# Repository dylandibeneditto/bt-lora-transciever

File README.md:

# bt-lora-transciever

## SX1262 (LoRa)
(datasheet)
https://semtech.my.salesforce.com/sfc/p/#E0000000JelG/a/RQ000008nKCH/hp2iKwMDKWl34g1D3LBf_zC7TGBRIo2ff5LMnS8r19s
(application notes)
https://cdn-reichelt.de/documents/datenblatt/A200/SX1262REFERENCE.pdf

## Matching Network IC (0900FM15K0039001E)
https://www.johansontechnology.com/docs/1646/0900FM15K0039001E_rIWs6SY.pdf
https://www.johansontechnology.com/docs/2424/oldjti-an100_kC6DtU1.pdf

## nRF21540 (Bluetooth Range Extender)
https://docs.nordicsemi.com/r/bundle/ps_nrf21540/page/chapters/hw_layout/reference_circuitry/doc/alt1.html

## nRF52840
https://docs.nordicsemi.com/r/bundle/ps_nrf52840/page/keyfeatures_html5.html

## 3.3V LDO (LD39200)
https://www.st.com/content/ccc/resource/technical/document/datasheet/4b/e6/2e/a4/16/04/46/9d/DM00102135.pdf/files/DM00102135.pdf/jcr:content/translations/en.DM00102135.pdf

## 5V Buck (TPS51386)
https://www.ti.com/lit/ds/symlink/tps51386.pdf?ts=1792470785772&ref_url=https%253A%252F%252Fwww.ti.com%252Fproduct%252FTPS51386%252Fpart-details%252FTPS51386RJNR%253Futm_source%253Dgoogle%2526utm_medium%253Dcpc%2526utm_campaign%253Dapp-null-null-app_opn_en-cpc-storeic-google-ww_en_pur%2526utm_content%253DDevice%2526ds_k%253DTPS51386RJNR%2526DCM%253Dyes%2526gclsrc%253Daw.ds%2526gad_source%253D1%2526gad_campaignid%253D18950597671%2526gbraid%253D0AAAAAC068F2AgVPJnnzCa5HBOf_R-twsL%2526gclid%253DCjwKCAjw_9bWBhBGEiwAomyTIuwXhYG7RjTolWD5RO6H10wT5wzYAQIXjeRW8OVubMzsjR8nUko-0RoCKO8QAvD_BwE

## TCXO (ECS-TXO-20SCMV4)
https://ecsxtal.com/store/pdf/ECS-TXO-20CSMV4.pdf

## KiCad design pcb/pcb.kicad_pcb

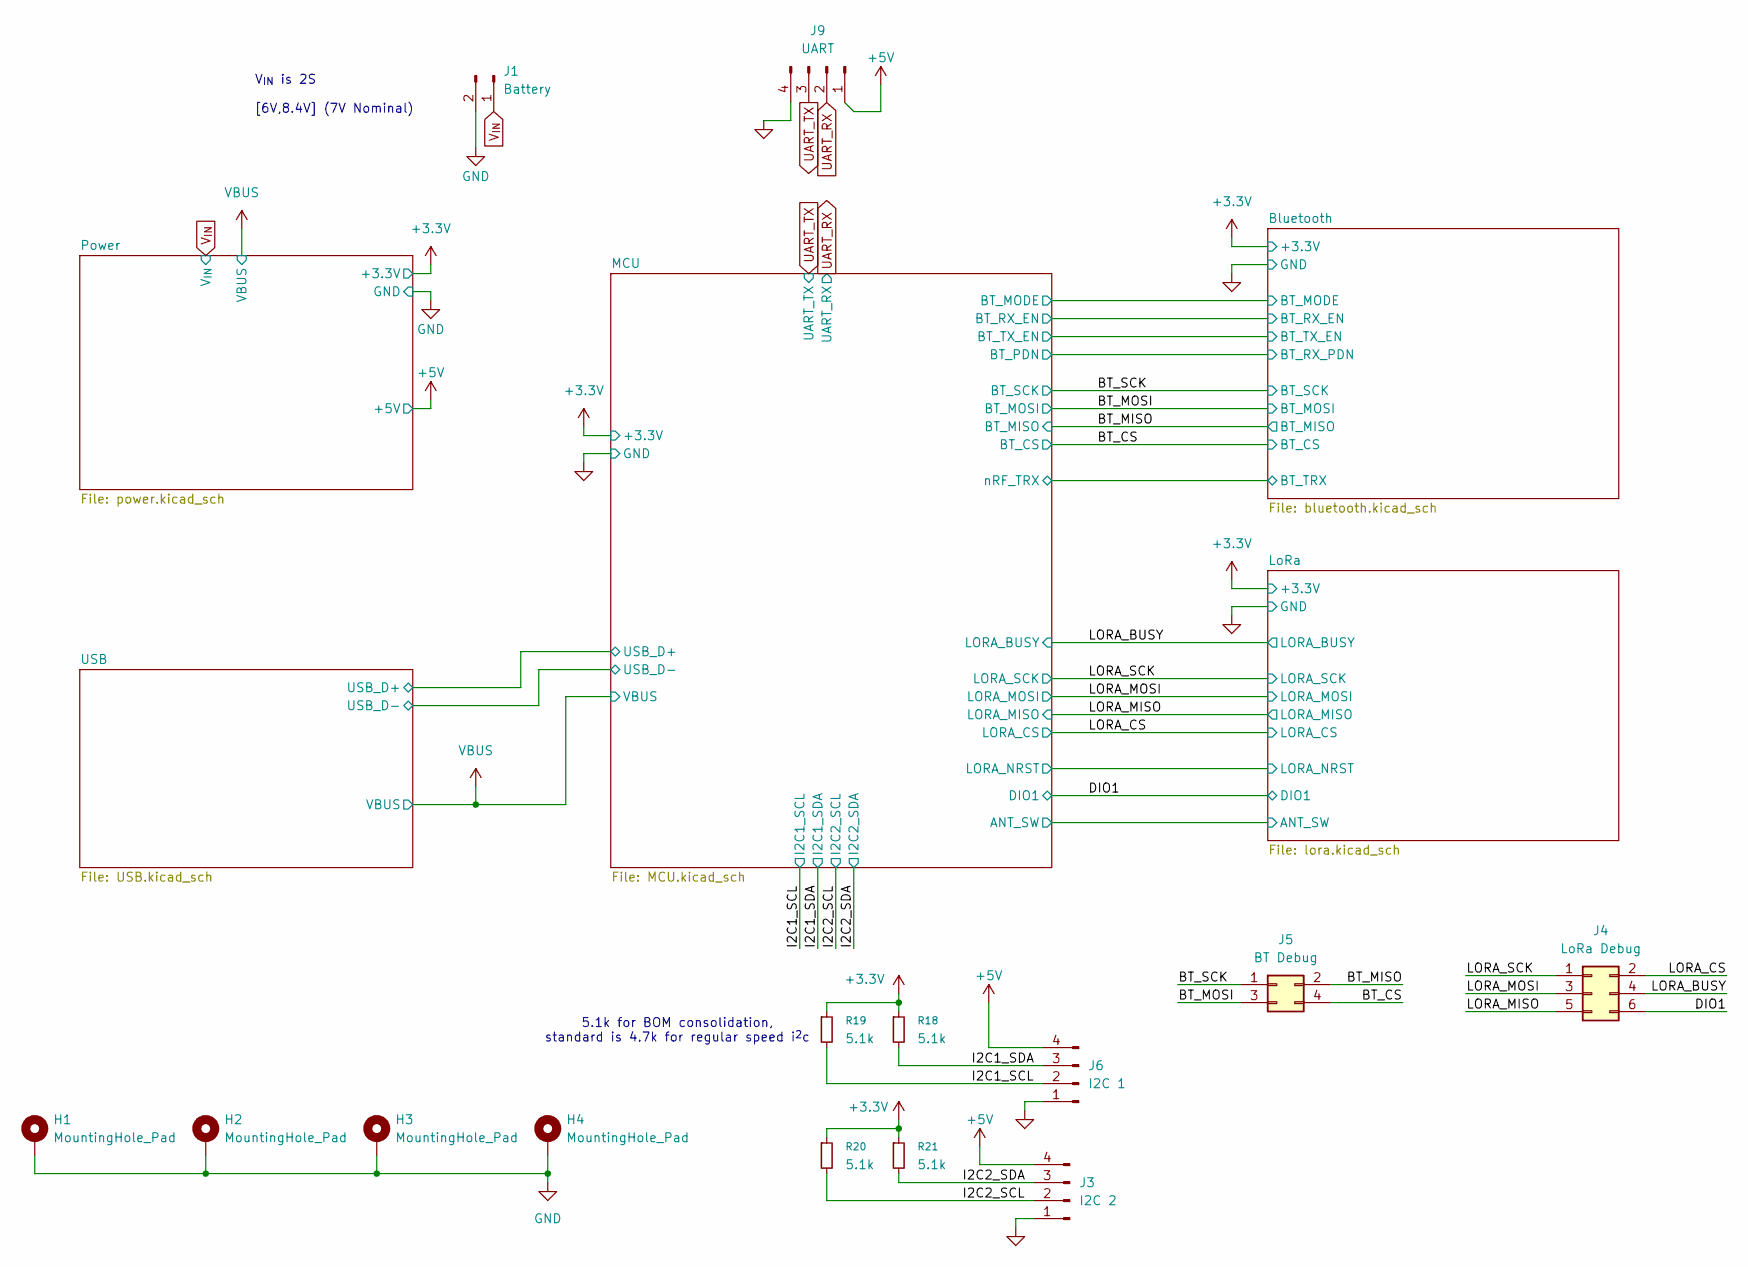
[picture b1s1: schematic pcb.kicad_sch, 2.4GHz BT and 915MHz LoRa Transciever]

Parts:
H1, H2, H3, H4: MountingHole_Pad; MountingHole_2.2mm_M2_Pad_Via
J1: Battery; JST_GH_SM02B-GHS-TB_1x02-1MP_P1.25mm_Horizontal
J3: I2C 2; JST_GH_SM04B-GHS-TB_1x04-1MP_P1.25mm_Horizontal
J4: LoRa Debug; PinHeader_2x03_P2.54mm_Vertical
J5: BT Debug; PinHeader_2x02_P2.54mm_Vertical
J6: I2C 1; JST_GH_SM04B-GHS-TB_1x04-1MP_P1.25mm_Horizontal
J9: UART; JST_GH_SM04B-GHS-TB_1x04-1MP_P1.25mm_Horizontal
R18, R19, R20, R21: 5.1k; R_0603_1608Metric

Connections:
+3.3V: R18.1, R19.1, R20.1, R21.1; also elsewhere on the board
+5V: J3.4, J6.4, J9.1; also elsewhere on the board
BT_CS: J5.4; also elsewhere on the board
BT_MISO: J5.2; also elsewhere on the board
BT_MOSI: J5.3; also elsewhere on the board
BT_SCK: J5.1; also elsewhere on the board
DIO1: J4.6; also elsewhere on the board
GND: H1.1 (1_1), H2.1 (1_1), H3.1 (1_1), H4.1 (1_1), J1.2, J3.1, J6.1, J9.4; also elsewhere on the board
I2C1_SCL: J6.2, R19.2; also elsewhere on the board
I2C1_SDA: J6.3, R18.2; also elsewhere on the board
I2C2_SCL: J3.2, R20.2; also elsewhere on the board
I2C2_SDA: J3.3, R21.2; also elsewhere on the board
LORA_BUSY: J4.4; also elsewhere on the board
LORA_CS: J4.2; also elsewhere on the board
LORA_MISO: J4.5; also elsewhere on the board
LORA_MOSI: J4.3; also elsewhere on the board
LORA_SCK: J4.1; also elsewhere on the board
UART_RX: J9.2; also elsewhere on the board
UART_TX: J9.3; also elsewhere on the board
V_{IN}: J1.1; also elsewhere on the board

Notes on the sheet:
V_{IN} is 2S [6V,8.4V] (7V Nominal)
5.1k for BOM consolidation, standard is 4.7k for regular speed i^{2}c

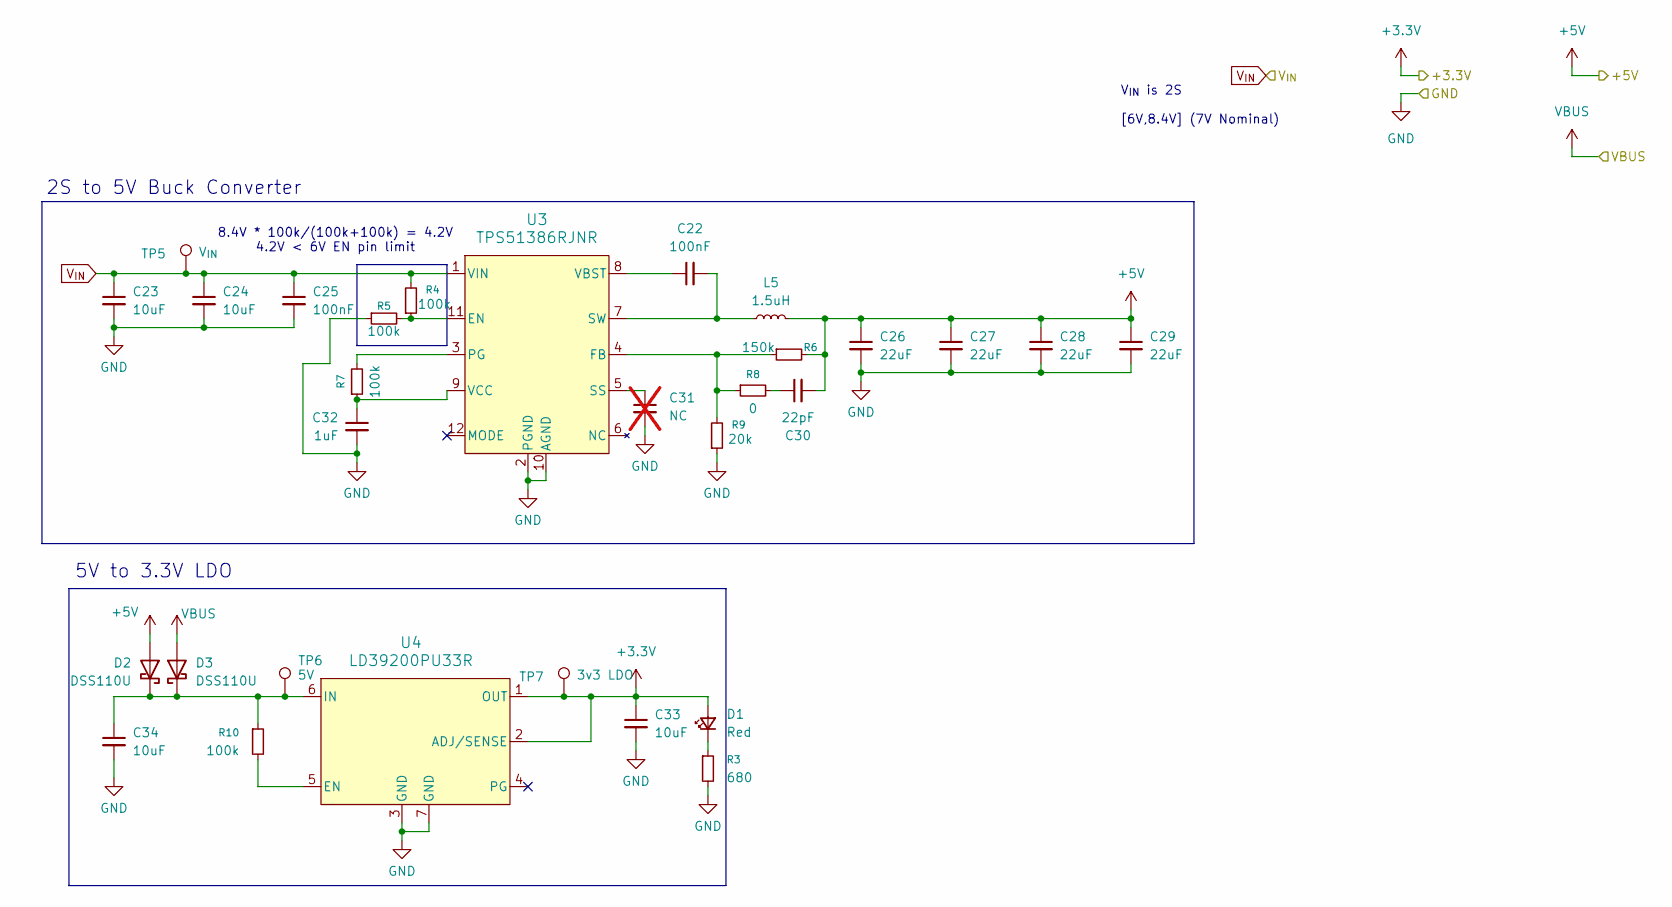
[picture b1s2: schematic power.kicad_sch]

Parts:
C22, C25: 100nF; C_0402_1005Metric
C23, C24, C33, C34: 10uF; C_0805_2012Metric
C26, C27, C28, C29: 22uF; C_0805_2012Metric
C30: 22pF; C_0402_1005Metric
C31: NC; C_0805_2012Metric; not fitted
C32: 1uF; C_0805_2012Metric
D1: Red; LED_0603_1608Metric
D2, D3: DSS110U; D_SOD-123F
L5: 1.5uH; L_Coilcraft_XAL6030-XXX
R3: 680; R_0603_1608Metric
R4, R5, R7, R10: 100k; R_0603_1608Metric
R6: 150k; R_0603_1608Metric
R8: 0; R_0603_1608Metric
R9: 20k; R_0603_1608Metric
TP5: V_{IN}; TestPoint_Pad_D1.0mm
TP6: 5V; TestPoint_Pad_D1.0mm
TP7: 3v3 LDO; TestPoint_Pad_D1.0mm
U3: TPS51386RJNR; VQFN-HR12_RJN_TEX
U4: LD39200PU33R; SON_DFN6_3X3_STM

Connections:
+3.3V: C33.1, D1.2 (A), TP7.1 (1_1), U4.1 (OUT), U4.2 (ADJ/SENSE); also elsewhere on the board
+5V: C26.1, C27.1, C28.1, C29.1, C30.2, D2.2 (A), L5.2, R6.2; also elsewhere on the board
GND: C23.2, C24.2, C25.2, C26.2, C27.2, C28.2, C29.2, C31.2, C32.2, C33.2, C34.2, R3.2, R5.1, R9.1, U3.2 (PGND), U3.10 (AGND), U4.3 (GND), U4.7 (GND); also elsewhere on the board
unnamed: C30.1, R8.2
unnamed: D1.1 (K), R3.1
unnamed: C34.1, D2.1 (K), D3.1 (K), R10.1, TP6.1 (1_1), U4.6 (IN)
unnamed: R4.1, R5.2, U3.11 (EN)
unnamed: R6.1, R8.1, R9.2, U3.4 (FB)
unnamed: R7.2, U3.3 (PG)
unnamed: C31.1, U3.5 (SS)
unnamed: C22.2, L5.1, U3.7 (SW)
unnamed: C22.1, U3.8 (VBST)
unnamed: C32.1, R7.1, U3.9 (VCC)
unnamed: R10.2, U4.5 (EN)
VBUS: D3.2 (A); also elsewhere on the board
V_{IN}: C23.1, C24.1, C25.1, R4.2, TP5.1 (1_1), U3.1 (VIN); also elsewhere on the board

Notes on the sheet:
2S to 5V Buck Converter
V_{IN} is 2S [6V,8.4V] (7V Nominal)
5V to 3.3V LDO
8.4V * 100k/(100k+100k) = 4.2V 4.2V < 6V EN pin limit

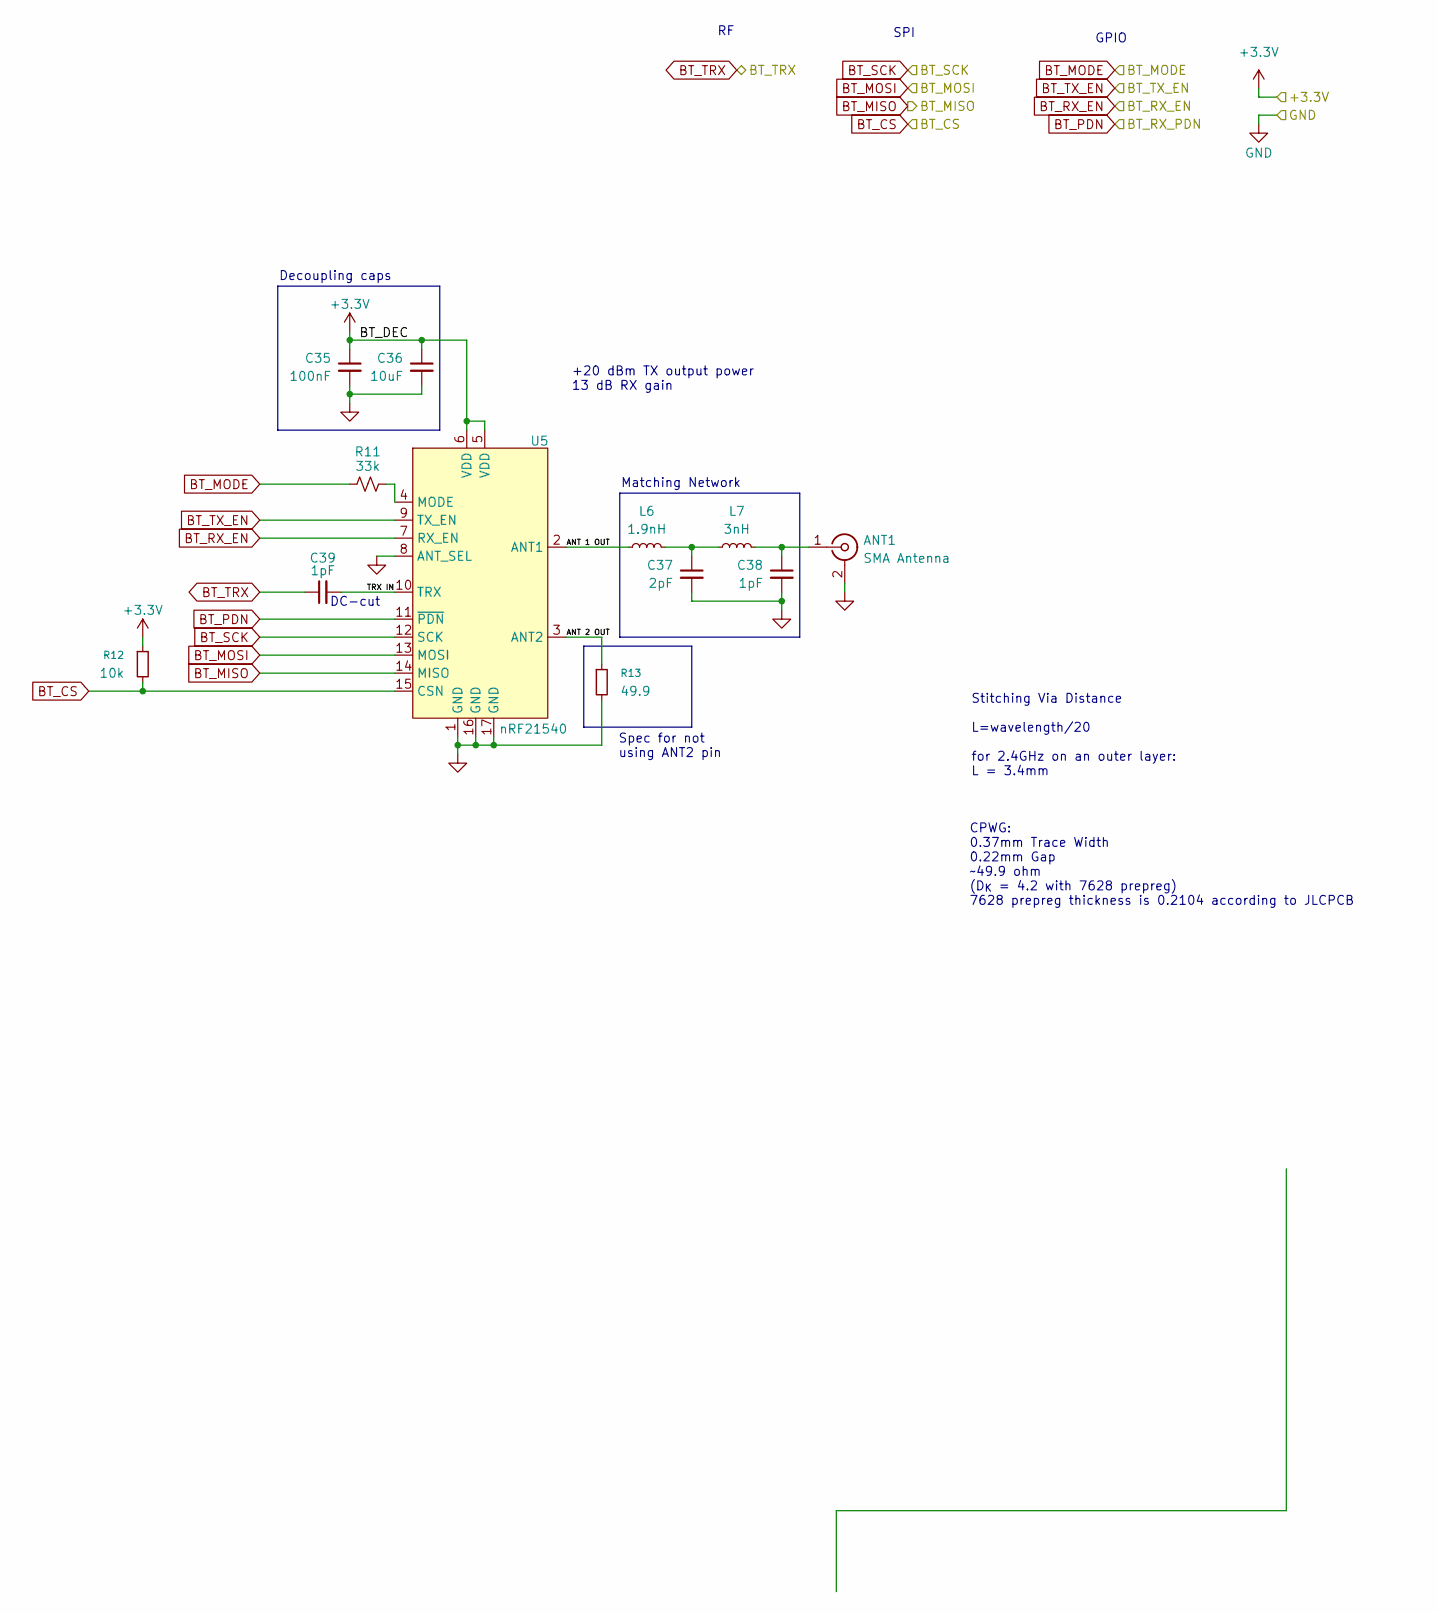
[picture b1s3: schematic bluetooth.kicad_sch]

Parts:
ANT1: SMA Antenna; SMA_Molex_73251-2120_EdgeMount_Horizontal
C35: 100nF; C_0402_1005Metric
C36: 10uF; C_0603_1608Metric
C37: 2pF; C_0402_1005Metric
C38, C39: 1pF; C_0402_1005Metric
L6: 1.9nH; L_0402_1005Metric
L7: 3nH; L_0402_1005Metric
R11: 33k; R_0603_1608Metric
R12: 10k; R_0603_1608Metric
R13: 49.9; R_0603_1608Metric
U5: nRF21540; QFN-16-1EP_4x4mm_P0.65mm_EP2.7x2.7mm

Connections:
+3.3V: C35.1, C36.1, R12.1, U5.5 (VDD), U5.6 (VDD); also elsewhere on the board
/Bluetooth/ANT 1 OUT: L6.1, U5.2 (ANT1)
/Bluetooth/ANT 2 OUT: R13.1, U5.3 (ANT2)
/Bluetooth/TRX IN: C39.2, U5.10 (TRX)
BT_CS: R12.2, U5.15 (CSN); also elsewhere on the board
BT_MISO: U5.14 (MISO); also elsewhere on the board
BT_MODE: R11.1; also elsewhere on the board
BT_MOSI: U5.13 (MOSI); also elsewhere on the board
BT_PDN: U5.11 (~PDN); also elsewhere on the board
BT_RX_EN: U5.7 (RX_EN); also elsewhere on the board
BT_SCK: U5.12 (SCK); also elsewhere on the board
BT_TX_EN: U5.9 (TX_EN); also elsewhere on the board
GND: ANT1.2 (Ext), C35.2, C36.2, C37.2, C38.2, R13.2, U5.1 (GND), U5.8 (ANT_SEL), U5.16 (GND), U5.17 (GND); also elsewhere on the board
unnamed: ANT1.1 (In), C38.1, L7.2
unnamed: C37.1, L6.2, L7.1
unnamed: R11.2, U5.4 (MODE)
nRF_TRX: C39.1; also elsewhere on the board

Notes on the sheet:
CPWG: 0.37mm Trace Width 0.22mm Gap ~49.9 ohm (D_{K} = 4.2 with 7628 prepreg) 7628 prepreg thickness is 0.2104 according to JLCPCB
SPI
DC-cut
+20 dBm TX output power 13 dB RX gain
Spec for not using ANT2 pin
Matching Network
Stitching Via Distance L=wavelength/20 for 2.4GHz on an outer layer: L = 3.4mm
GPIO
Decoupling caps

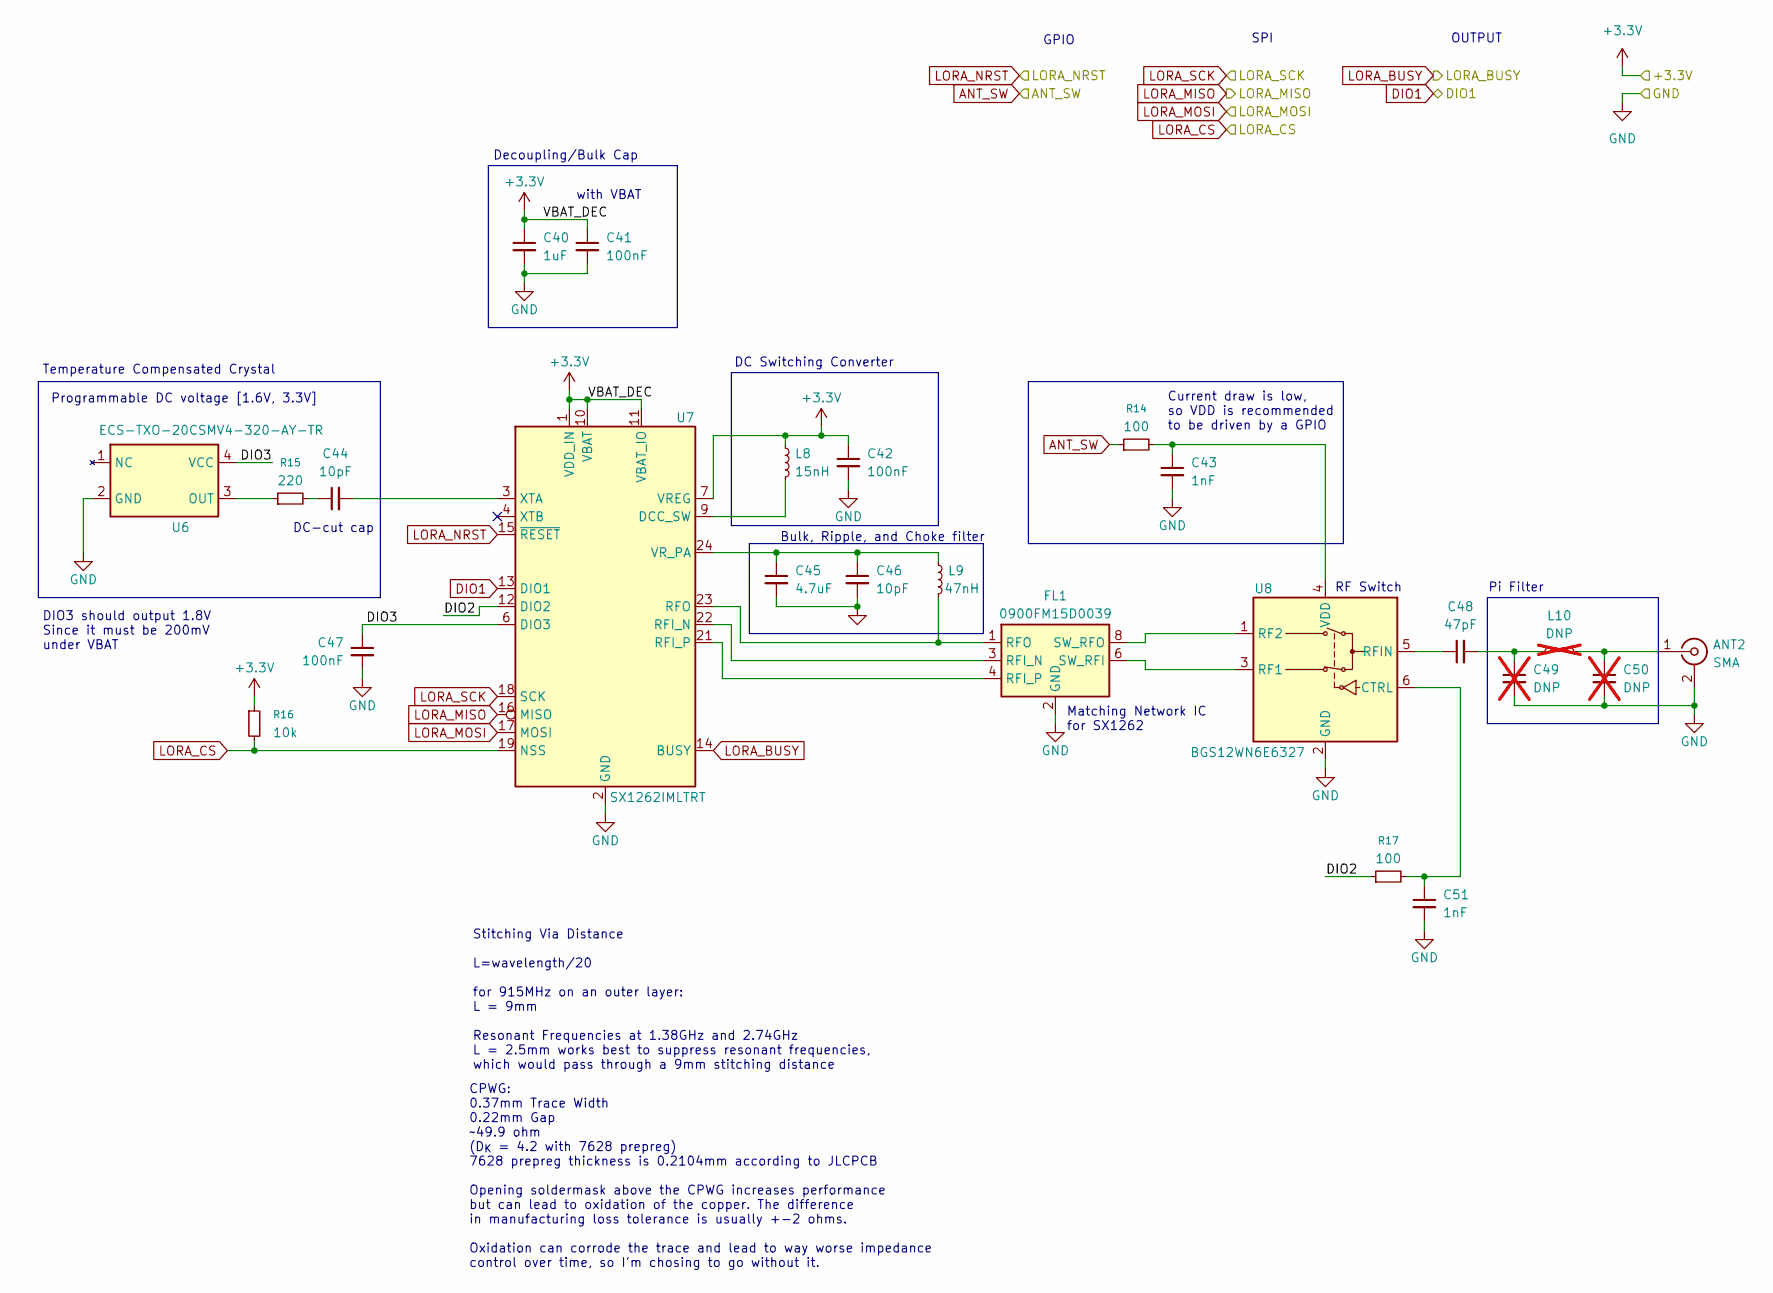
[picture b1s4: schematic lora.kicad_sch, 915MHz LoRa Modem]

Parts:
ANT2: SMA; SMA_Molex_73251-2120_EdgeMount_Horizontal
C40: 1uF; C_0603_1608Metric
C41, C42, C47: 100nF; C_0402_1005Metric
C43, C51: 1nF; C_0402_1005Metric
C44, C46: 10pF; C_0402_1005Metric
C45: 4.7uF; C_0603_1608Metric
C48: 47pF; C_0402_1005Metric
C49, C50: DNP; C_0402_1005Metric; not fitted
FL1: 0900FM15D0039; Balun_Johanson_0900FM15K0039
L8: 15nH; L_0402_1005Metric
L9: 47nH; L_0402_1005Metric
L10: DNP; L_0402_1005Metric; not fitted
R14, R17: 100; R_0603_1608Metric
R15: 220; R_0603_1608Metric
R16: 10k; R_0603_1608Metric
U6: ECS-TXO-20CSMV4-320-AY-TR; Oscillator_SMD_ECS_2016
U7: SX1262IMLTRT; QFN-24-1EP_4x4mm_P0.5mm_EP2.6x2.6mm
U8: BGS12WN6E6327; Infineon_PG-TSNP-6-10_0.7x1.1mm_0.7x1.1mm_P0.4mm

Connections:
+3.3V: C40.1, C41.1, C42.1, L8.1, R16.1, U7.1 (VDD_IN), U7.7 (VREG), U7.10 (VBAT), U7.11 (VBAT_IO); also elsewhere on the board
/LoRa/DIO2: R17.1, U7.12 (DIO2)
/LoRa/DIO3: C47.1, U6.4 (VCC), U7.6 (DIO3)
ANT_SW: R14.1; also elsewhere on the board
DIO1: U7.13 (DIO1); also elsewhere on the board
GND: ANT2.2 (Ext), C40.2, C41.2, C42.2, C43.2, C45.2, C46.2, C47.2, C49.2, C50.2, C51.2, FL1.2 (GND), FL1.5 (GND), FL1.7 (GND), FL1.9 (GND), FL1.10 (GND), U6.2 (GND), U7.2 (GND), U7.5 (GND), U7.8 (GND), U7.20 (GND), U7.25 (GND), U8.2 (GND); also elsewhere on the board
LORA_BUSY: U7.14 (BUSY); also elsewhere on the board
LORA_CS: R16.2, U7.19 (NSS); also elsewhere on the board
LORA_MISO: U7.16 (MISO); also elsewhere on the board
LORA_MOSI: U7.17 (MOSI); also elsewhere on the board
LORA_NRST: U7.15 (~RESET); also elsewhere on the board
LORA_SCK: U7.18 (SCK); also elsewhere on the board
unnamed: ANT2.1 (In), C50.1, L10.2
unnamed: C44.1, R15.2
unnamed: C48.2, C49.1, L10.1
unnamed: FL1.3 (RFI_N), U7.22 (RFI_N)
unnamed: FL1.4 (RFI_P), U7.21 (RFI_P)
unnamed: FL1.1 (RFO), L9.2, U7.23 (RFO)
unnamed: FL1.6 (SW_RFI), U8.3 (RF1)
unnamed: FL1.8 (SW_RFO), U8.1 (RF2)
unnamed: R15.1, U6.3 (OUT)
unnamed: L8.2, U7.9 (DCC_SW)
unnamed: C45.1, C46.1, L9.1, U7.24 (VR_PA)
unnamed: C44.2, U7.3 (XTA)
unnamed: C51.1, R17.2, U8.6 (CTRL)
unnamed: C48.1, U8.5 (RFIN)
unnamed: C43.1, R14.2, U8.4 (VDD)

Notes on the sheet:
Matching Network IC for SX1262
DC-cut cap
Pi Filter
DIO3 should output 1.8V Since it must be 200mV under VBAT
Temperature Compensated Crystal
Current draw is low, so VDD is recommended to be driven by a GPIO
GPIO
RF Switch
Stitching Via Distance L=wavelength/20 for 915MHz on an outer layer: L = 9mm Resonant Frequencies at 1.38GHz and 2.74GHz L = 2.5mm works best to suppress resonant frequencies, which would pass through a 9mm stitching distance
OUTPUT
Decoupling/Bulk Cap
with VBAT
DC Switching Converter
SPI
Bulk, Ripple, and Choke filter
CPWG: 0.37mm Trace Width 0.22mm Gap ~49.9 ohm (D_{K} = 4.2 with 7628 prepreg) 7628 prepreg thickness is 0.2104mm according to JLCPCB Opening soldermask above the CPWG increases performance but can lead to oxidation of the copper. The difference in manufacturing loss tolerance is usually +-2 ohms. O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
Programmable DC voltage [1.6V, 3.3V]

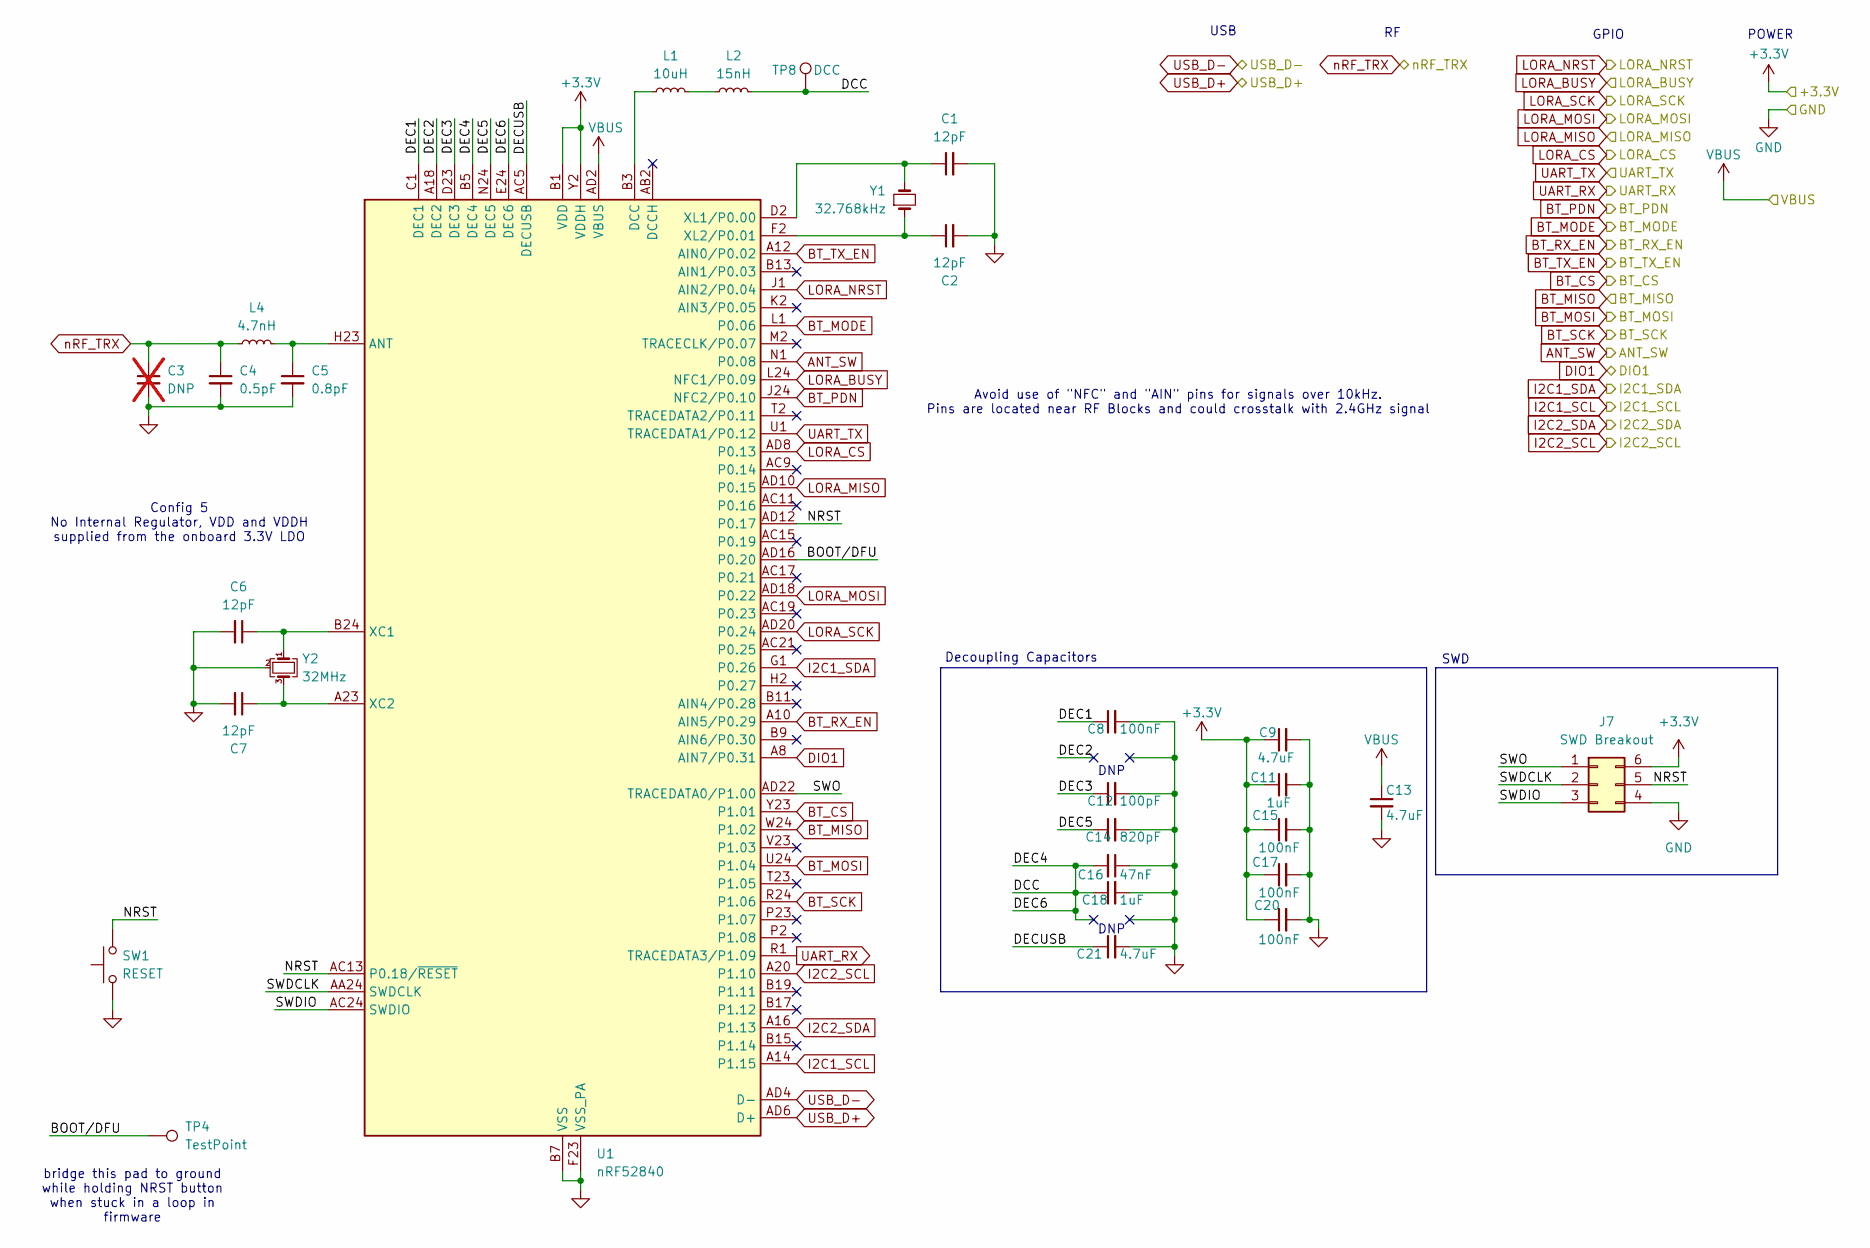
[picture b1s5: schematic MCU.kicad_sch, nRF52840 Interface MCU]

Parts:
C1, C2, C6, C7: 12pF; C_0402_1005Metric; LCSC Part Number C1547
C3: DNP; C_0402_1005Metric; not fitted
C4: 0.5pF; C_0402_1005Metric; LCSC Part Number C1544
C5: 0.8pF; C_0402_1005Metric; LCSC Part Number C88902
C8, C15, C17, C20: 100nF; C_0402_1005Metric; LCSC Part Number C1525
C9, C13, C21: 4.7uF; C_0603_1608Metric; LCSC Part Number C1779
C11, C18: 1uF; C_0603_1608Metric; LCSC Part Number C15849
C12: 100pF; C_0402_1005Metric; LCSC Part Number C1546
C14: 820pF; C_0402_1005Metric; LCSC Part Number C1543
C16: 47nF; C_0402_1005Metric; LCSC Part Number C82219
J7: SWD Breakout; PinHeader_2x03_P2.54mm_Vertical
L1: 10uH; L_0603_1608Metric; LCSC Part Number C1035
L2: 15nH; L_0402_1005Metric; LCSC Part Number C86059
L4: 4.7nH; L_0402_1005Metric; LCSC Part Number C86065
SW1: RESET; SW_Push_SPST_NO_Alps_SKRK; LCSC Part Number C720477
TP4: TestPoint; TestPoint_Pad_D1.0mm
TP8: DCC; TestPoint_Pad_D1.0mm
U1: nRF52840; Nordic_AQFN-73-1EP_7x7mm_P0.5mm
Y1: 32.768kHz; Crystal_SMD_3215-2Pin_3.2x1.5mm; LCSC Part Number C32346
Y2: 32MHz; Crystal_SMD_3225-4Pin_3.2x2.5mm; LCSC Part Number C9009

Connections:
+3.3V: C9.1, C11.1, C15.1, C17.1, C20.1, J7.6, U1.A22 (VDD), U1.AD14 (VDD), U1.AD23 (VDD), U1.B1 (VDD), U1.W1 (VDD), U1.Y2 (VDDH); also elsewhere on the board
/MCU/BOOT/DFU: TP4.1 (1_1), U1.AD16 (P0.20)
/MCU/DCC: C16.2, C18.1, L2.2, TP8.1 (1_1), U1.B5 (DEC4), U1.E24 (DEC6)
/MCU/DEC1: C8.1, U1.C1 (DEC1)
/MCU/DEC2: U1.A18 (DEC2)
/MCU/DEC3: C12.1, U1.D23 (DEC3)
/MCU/DEC5: C14.1, U1.N24 (DEC5)
/MCU/DECUSB: C21.1, U1.AC5 (DECUSB)
/MCU/NRST: J7.5, SW1.2, U1.AC13 (P0.18/~RESET), U1.AD12 (P0.17)
/MCU/SWDCLK: J7.2, U1.AA24 (SWDCLK)
/MCU/SWDIO: J7.3, U1.AC24 (SWDIO)
/MCU/SWO: J7.1, U1.AD22 (TRACEDATA0/P1.00)
ANT_SW: U1.N1 (P0.08); also elsewhere on the board
BT_CS: U1.Y23 (P1.01); also elsewhere on the board
BT_MISO: U1.W24 (P1.02); also elsewhere on the board
BT_MODE: U1.L1 (P0.06); also elsewhere on the board
BT_MOSI: U1.U24 (P1.04); also elsewhere on the board
BT_PDN: U1.J24 (NFC2/P0.10); also elsewhere on the board
BT_RX_EN: U1.A10 (AIN5/P0.29); also elsewhere on the board
BT_SCK: U1.R24 (P1.06); also elsewhere on the board
BT_TX_EN: U1.A12 (AIN0/P0.02); also elsewhere on the board
DIO1: U1.A8 (AIN7/P0.31); also elsewhere on the board
GND: C1.2, C2.2, C3.2, C4.2, C5.2, C6.2, C7.2, C8.2, C9.2, C11.2, C12.2, C13.2, C14.2, C15.2, C16.1, C17.2, C18.2, C20.2, C21.2, J7.4, SW1.1, U1.B7 (VSS), U1.EP (VSS), U1.F23 (VSS_PA), Y2.2 (G), Y2.4 (G); also elsewhere on the board
I2C1_SCL: U1.A14 (P1.15); also elsewhere on the board
I2C1_SDA: U1.G1 (P0.26); also elsewhere on the board
I2C2_SCL: U1.A20 (P1.10); also elsewhere on the board
I2C2_SDA: U1.A16 (P1.13); also elsewhere on the board
LORA_BUSY: U1.L24 (NFC1/P0.09); also elsewhere on the board
LORA_CS: U1.AD8 (P0.13); also elsewhere on the board
LORA_MISO: U1.AD10 (P0.15); also elsewhere on the board
LORA_MOSI: U1.AD18 (P0.22); also elsewhere on the board
LORA_NRST: U1.J1 (AIN2/P0.04); also elsewhere on the board
LORA_SCK: U1.AD20 (P0.24); also elsewhere on the board
unnamed: L1.2, L2.1
unnamed: C5.1, L4.2, U1.H23 (ANT)
unnamed: L1.1, U1.B3 (DCC)
unnamed: C6.1, U1.B24 (XC1), Y2.1
unnamed: C7.1, U1.A23 (XC2), Y2.3
unnamed: C1.1, U1.D2 (XL1/P0.00), Y1.2
unnamed: C2.1, U1.F2 (XL2/P0.01), Y1.1
UART_RX: U1.R1 (TRACEDATA3/P1.09); also elsewhere on the board
UART_TX: U1.U1 (TRACEDATA1/P0.12); also elsewhere on the board
USB_D+: U1.AD6 (D+); also elsewhere on the board
USB_D-: U1.AD4 (D-); also elsewhere on the board
VBUS: C13.1, U1.AD2 (VBUS); also elsewhere on the board
nRF_TRX: C3.1, C4.1, L4.1; also elsewhere on the board

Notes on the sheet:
POWER
SWD
DNP
GPIO
bridge this pad to ground while holding NRST button when stuck in a loop in firmware
Decoupling Capacitors
Avoid use of "NFC" and "AIN" pins for signals over 10kHz. Pins are located near RF Blocks and could crosstalk with 2.4GHz signal
Config 5 No Internal Regulator, VDD and VDDH supplied from the onboard 3.3V LDO
USB

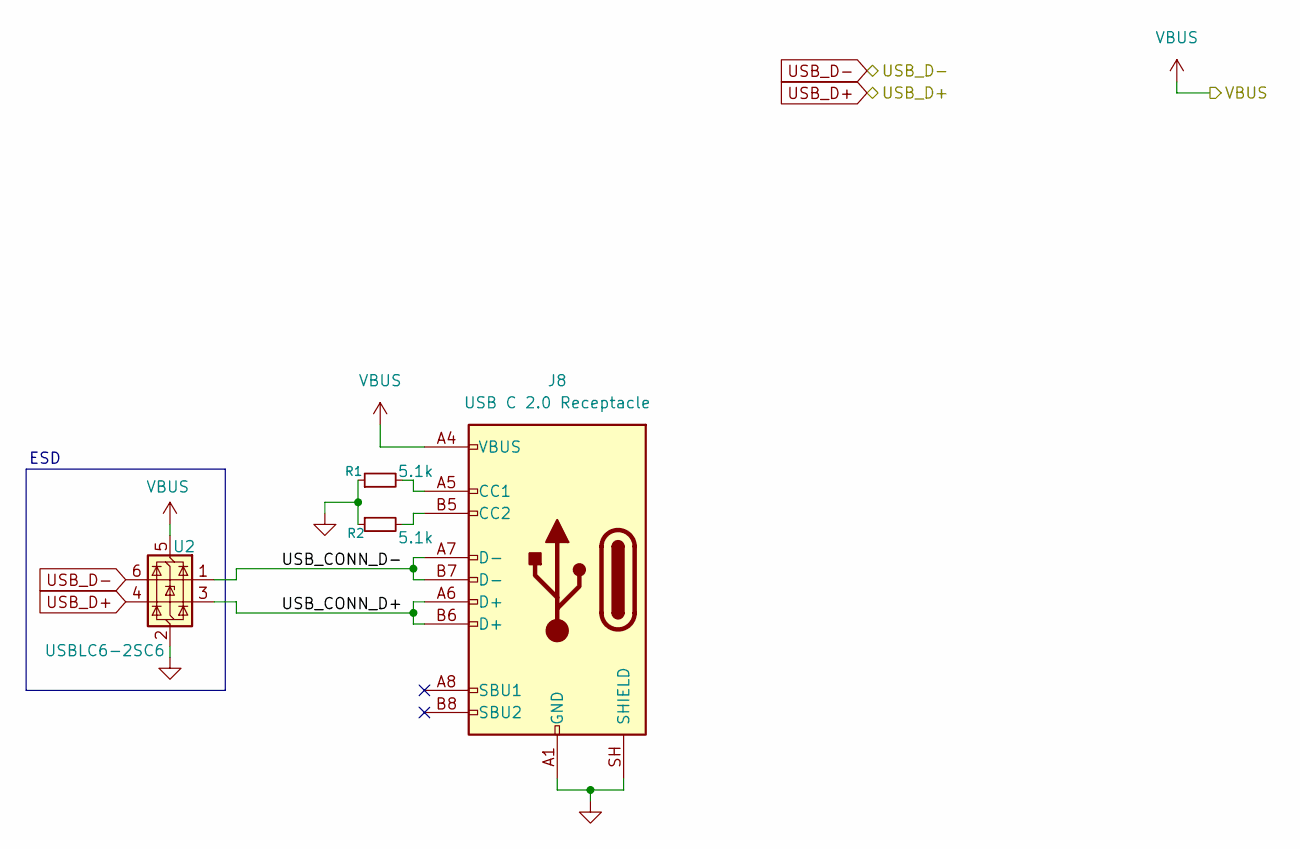
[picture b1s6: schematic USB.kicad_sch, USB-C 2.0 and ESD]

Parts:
J8: USB C 2.0 Receptacle; USB_C_Receptacle_HRO_TYPE-C-31-M-12
R1, R2: 5.1k; R_0603_1608Metric
U2: USBLC6-2SC6; SOT-23-6

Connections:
/USB/USB_CONN_D+: J8.A6 (D+), J8.B6 (D+), U2.3 (I/O2)
/USB/USB_CONN_D-: J8.A7 (D-), J8.B7 (D-), U2.1 (I/O1)
GND: J8.A1 (GND), J8.A12 (GND), J8.B1 (GND), J8.B12 (GND), J8.SH (SHIELD), R1.1, R2.1, U2.2 (GND); also elsewhere on the board
unnamed: J8.A5 (CC1), R1.2
unnamed: J8.B5 (CC2), R2.2
USB_D+: U2.4 (I/O2); also elsewhere on the board
USB_D-: U2.6 (I/O1); also elsewhere on the board
VBUS: J8.A4 (VBUS), J8.A9 (VBUS), J8.B4 (VBUS), J8.B9 (VBUS), U2.5 (VBUS); also elsewhere on the board

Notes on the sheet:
ESD

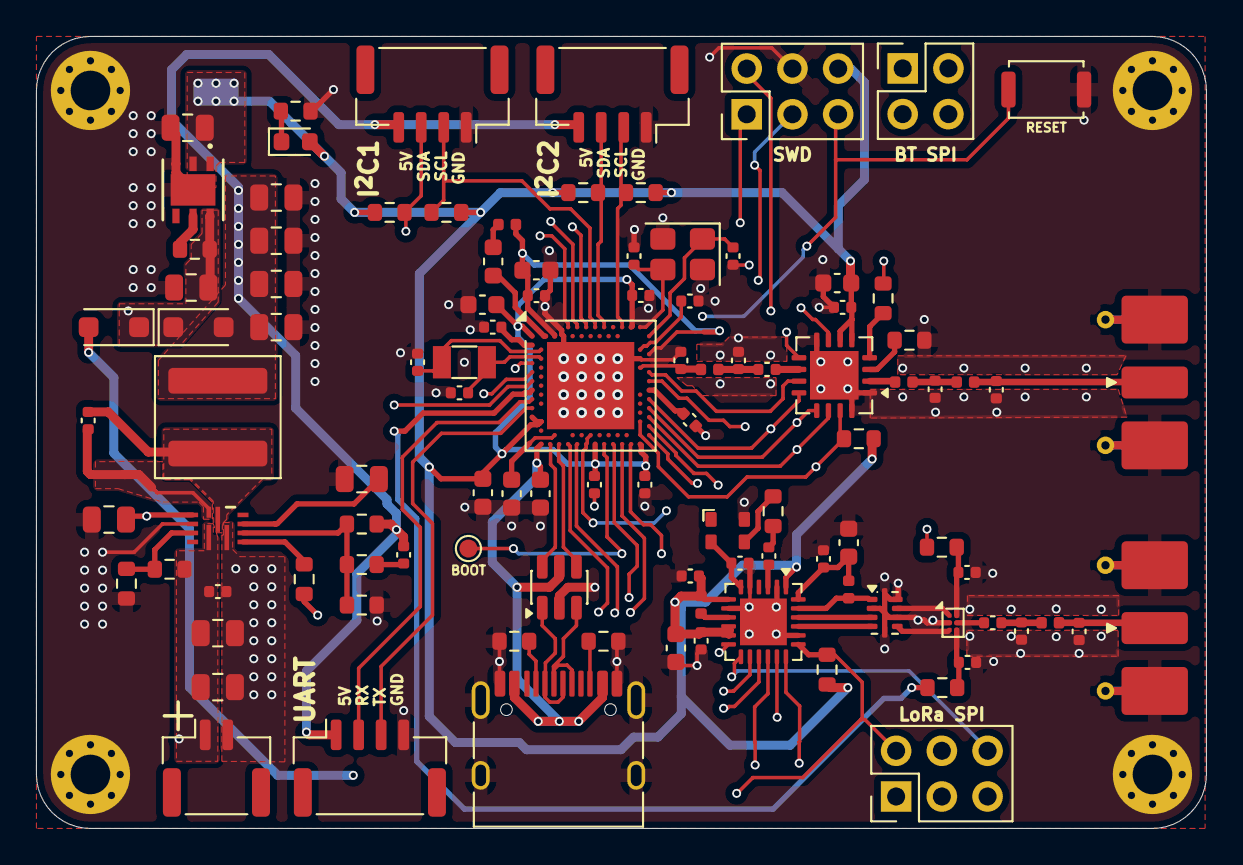
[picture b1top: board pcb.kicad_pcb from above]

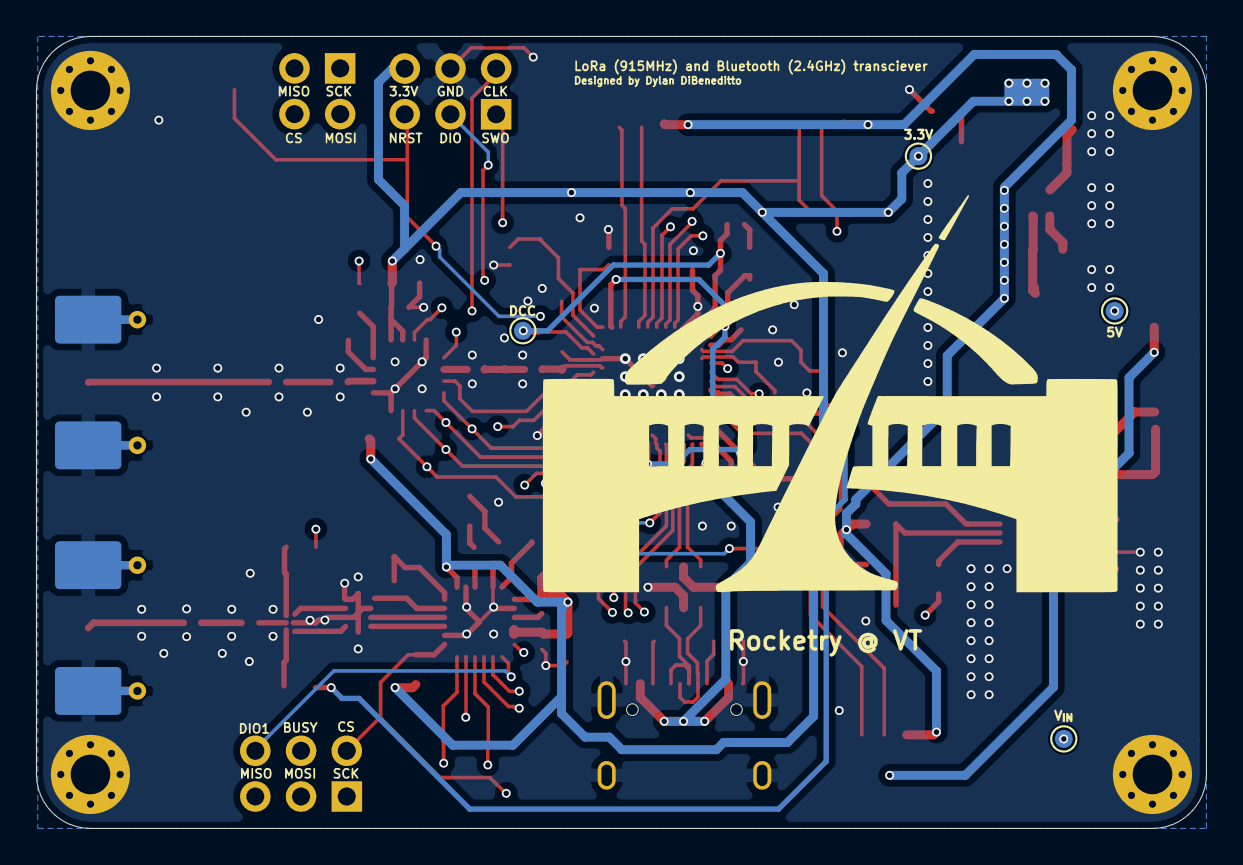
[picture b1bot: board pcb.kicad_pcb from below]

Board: 4 copper layers, 65.0 x 44.0 mm, 112 parts (4 on the bottom side), 85 nets.
